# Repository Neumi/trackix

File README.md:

# trackix bike tracker
trackix is an Arduino based LORAWAN / GPS tracker that fits into the rear light of a bicycle and pushes location data to The Things Network. This data can be fetched using the TTN API. 

Facts:
- Arduino based (Atmega 368 @ 8Mhz)
- super low power in standby
- GPS for localization
- RFM95 / SIM800l for communication
- 3.3v logic voltage
- 3.7v buffer battery
- charging from 6V bike dynamo
- embedded into rear light

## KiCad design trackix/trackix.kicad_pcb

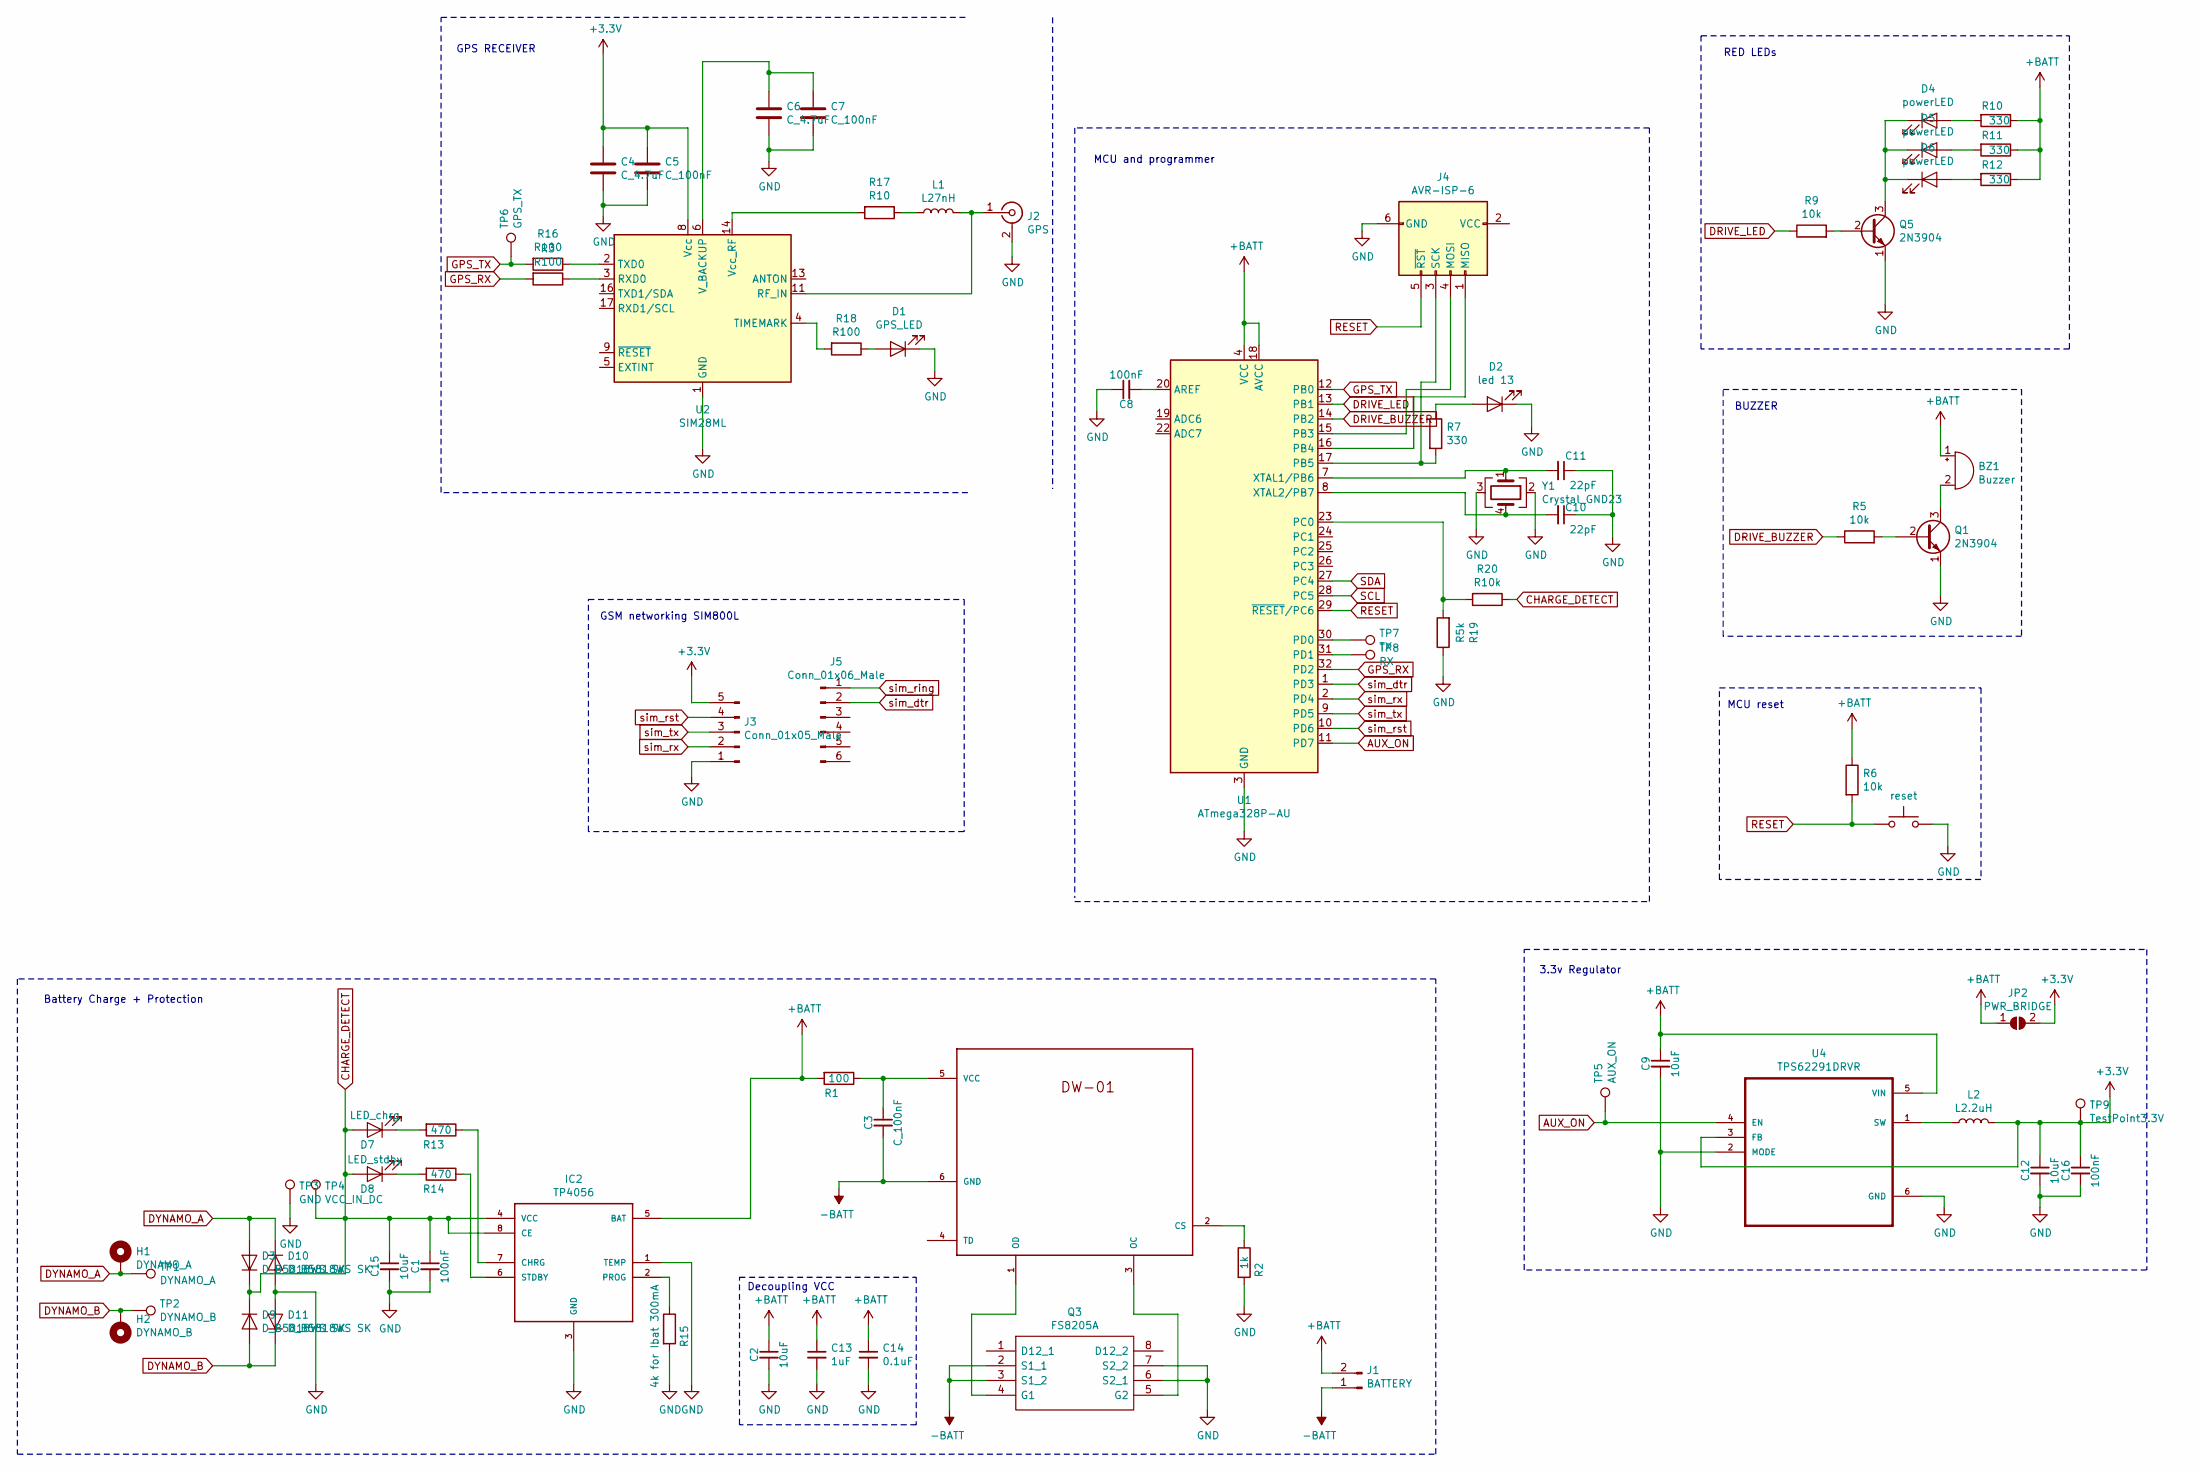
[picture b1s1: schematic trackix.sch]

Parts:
BZ1: Buzzer; Buzzer_Murata_PKMCS0909E4000-R1
C1, C8, C16: 100nF; C_0805
C2, C9, C12, C15: 10uF; C_1206
C3, C5, C7: C_100nF; C_0805
C4, C6: C_4.7uF; C_1206
C10, C11: 22pF; C_0805
C13: 1uF; C_1206
C14: 0.1uF; C_0805
D1: GPS_LED; LED_0805
D2: led 13; LED_0805
D3, D9, D10, D11: D_B5818WS SK; D_SOD-323
D4, D5: powerLED; LED_D5.0mm_Horizontal_O1.27mm_Z3.0mm
D6: powerLED; LED_D5.0mm
D7: LED_chrg; LED_0805
D8: LED_stdby; LED_0805
H1: DYNAMO_A; MountingHole_2.2mm_M2_ISO14580_Pad
H2: DYNAMO_B; MountingHole_2.2mm_M2_ISO14580_Pad
IC2: TP4056; HTSOP-8-1EP_3.9x4.9mm_Pitch1.27mm_ThermalVias_LargeCopper
J1: BATTERY; Pin_Header_Straight_1x02_Pitch2.54mm
J2: GPS; Molex_Microcoaxial_RF
J3: Conn_01x05_Male; Pin_Header_Straight_1x05_Pitch2.54mm
J4: AVR-ISP-6; Socket_Strip_Straight_2x03_Pitch2.54mm_SMD
J5: Conn_01x06_Male; Pin_Header_Straight_1x06_Pitch2.54mm
JP2: PWR_BRIDGE; SolderJumper-2_P1.3mm_Open_RoundedPad1.0x1.5mm
L1: L27nH; L_0402
L2: L2.2uH; L_1210
Q1, Q5: 2N3904; SOT-23W_Handsoldering
Q3: FS8205A; TSSOP-8_4.4x3mm_Pitch0.65mm; Manufacturer_Part_Number FS8205A
R1: 100; R_0805
R2: 1k; R_0805
R3, R16, R18: R100; R_0805
R5, R6, R9: 10k; R_0805
R7, R10, R11, R12: 330; R_0805
R13, R14: 470; R_0805
R15: 4k for Ibat 300mA; R_0805
R17: R10; R_0805
R19: R5k; R_0805
R20: R10k; R_0805
TP1: DYNAMO_A; Test_Point_Pad_1.0x1.0mm
TP2: DYNAMO_B; Test_Point_Pad_1.0x1.0mm
TP3: GND; Test_Point_Pad_1.0x1.0mm
TP4: VCC_IN_DC; Test_Point_Pad_1.0x1.0mm
TP5: AUX_ON; Test_Point_Pad_1.0x1.0mm
TP6: GPS_TX; Test_Point_Pad_1.0x1.0mm
TP7: TX; Test_Point_Pad_1.0x1.0mm
TP8: RX; Test_Point_Pad_1.0x1.0mm
TP9: TestPoint3.3V; Test_Point_Pad_1.0x1.0mm
U1: ATmega328P-AU; TQFP-32_7x7mm_Pitch0.8mm
U2: SIM28ML; XCVR_SIM28ML
U3: DW-01; TSOT-23-6
U4: TPS62291DRVR; SON65P200X200X80-7N
Y1: Crystal_GND23; Crystal_SMD_3225-4pin_3.2x2.5mm_HandSoldering
reset1: reset; SW_SPST_B3U-1000P

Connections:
+3V3: C4.1, C5.1, C12.1, C16.1, J3.5, JP2.2 (B), L2.2, TP9.1, U2.8 (Vcc), U4.3 (FB)
+BATT: BZ1.1 (-), C2.1, C9.1, C13.1, C14.1, IC2.5 (BAT), J1.2, JP2.1 (A), R1.2, R6.1, R10.1, R11.1, R12.1, U1.4 (VCC), U1.6 (VCC), U1.18 (AVCC), U4.5 (VIN)
-BATT: C3.2, J1.1, Q3.2 (S1_1), Q3.3 (S1_2), U3.6 (GND)
AUX_ON: TP5.1, U1.11 (PD7), U4.4 (EN)
CHARGE_DETECT: C1.1, C15.1, D3.1 (K), D7.2 (A), D8.2 (A), D9.1 (K), IC2.4 (VCC), IC2.8 (CE), R20.1, TP4.1
DRIVE_BUZZER: R5.1, U1.14 (PB2)
DRIVE_LED: R9.1, U1.13 (PB1)
DYNAMO_A: D3.2 (A), D10.1 (K), H1.1, TP1.1
DYNAMO_B: D9.2 (A), D11.1 (K), H2.1, TP2.1
GND: C1.2, C2.2, C4.2, C5.2, C6.2, C7.2, C8.1, C9.2, C10.1, C11.1, C12.2, C13.2, C14.2, C15.2, C16.2, D1.1 (K), D2.1 (K), D10.2 (A), D11.2 (A), IC2.1 (TEMP), IC2.3 (GND), J2.2 (Ext), J3.1, J4.6 (GND), Q1.1 (E), Q3.6 (S2_1), Q3.7 (S2_2), Q5.1 (E), R2.2, R15.2, R19.1, TP3.1, U1.3 (GND), U1.5 (GND), U1.21 (GND), U2.1 (GND), U2.10 (GND), U2.12 (GND), U4.2 (MODE), U4.6 (GND), Y1.2, Y1.3, reset1.2
GPS_RX: R3.2, U1.32 (PD2)
GPS_TX: R16.2, TP6.1, U1.12 (PB0)
unnamed 12: C11.2, U1.7 (XTAL1/PB6), Y1.1; also elsewhere on the board
unnamed 13: C10.2, U1.8 (XTAL2/PB7), Y1.4; also elsewhere on the board
unnamed: BZ1.2 (+), Q1.3 (C)
unnamed: C3.1, R1.1, U3.5 (VCC)
unnamed: C6.1, C7.1, U2.6 (V_BACKUP)
unnamed: C8.2, U1.20 (AREF)
unnamed: D1.2 (A), R18.1
unnamed: D2.2 (A), R7.1
unnamed: D4.1 (K), D5.1 (K), D6.1 (K), Q5.3 (C)
unnamed: D4.2 (A), R10.2
unnamed: D5.2 (A), R11.2
unnamed: D6.2 (A), R12.2
unnamed: D7.1 (K), R13.2
unnamed: D8.1 (K), R14.2
unnamed: IC2.2 (PROG), R15.1
unnamed: IC2.6 (STDBY), R14.1
unnamed: IC2.7 (CHRG), R13.1
unnamed: J2.1 (In), L1.2, U2.11 (RF_IN)
unnamed: J4.1 (MISO), U1.16 (PB4)
unnamed: J4.3 (SCK), R7.2, U1.17 (PB5)
unnamed: J4.4 (MOSI), U1.15 (PB3)
unnamed: L1.1, R17.1
unnamed: L2.1, U4.1 (SW)
unnamed: Q1.2 (B), R5.2
unnamed: Q3.4 (G1), U3.1 (OD)
unnamed: Q3.5 (G2), U3.3 (OC)
unnamed: Q5.2 (B), R9.2
unnamed: R2.1, U3.2 (CS)
unnamed: R3.1, U2.3 (RXD0)
unnamed: R16.1, U2.2 (TXD0)
unnamed: R17.2, U2.14 (Vcc_RF)
unnamed: R18.2, U2.4 (TIMEMARK)
unnamed: R19.2, R20.2, U1.23 (PC0)
unnamed: TP7.1, U1.30 (PD0)
unnamed: TP8.1, U1.31 (PD1)
RESET: J4.5 (~RST), R6.2, U1.29 (~RESET~/PC6), reset1.1
SCL: U1.28 (PC5)
SDA: U1.27 (PC4)
sim_dtr: J5.2, U1.1 (PD3)
sim_ring: J5.1
sim_rst: J3.4, U1.10 (PD6)
sim_rx: J3.2, U1.2 (PD4)
sim_tx: J3.3, U1.9 (PD5)

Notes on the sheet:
3.3v Regulator
Battery Charge + Protection
RED LEDs
BUZZER
Decoupling VCC
MCU reset
MCU and programmer
GSM networking SIM800L
GPS RECEIVER

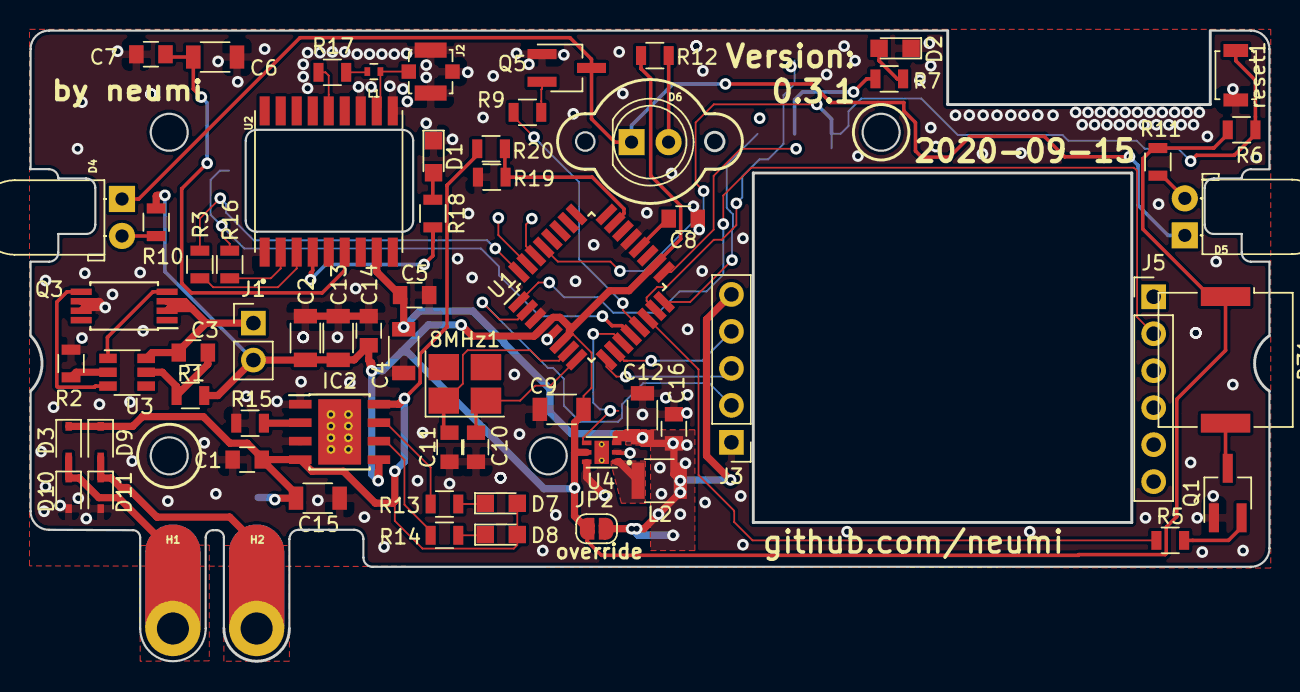
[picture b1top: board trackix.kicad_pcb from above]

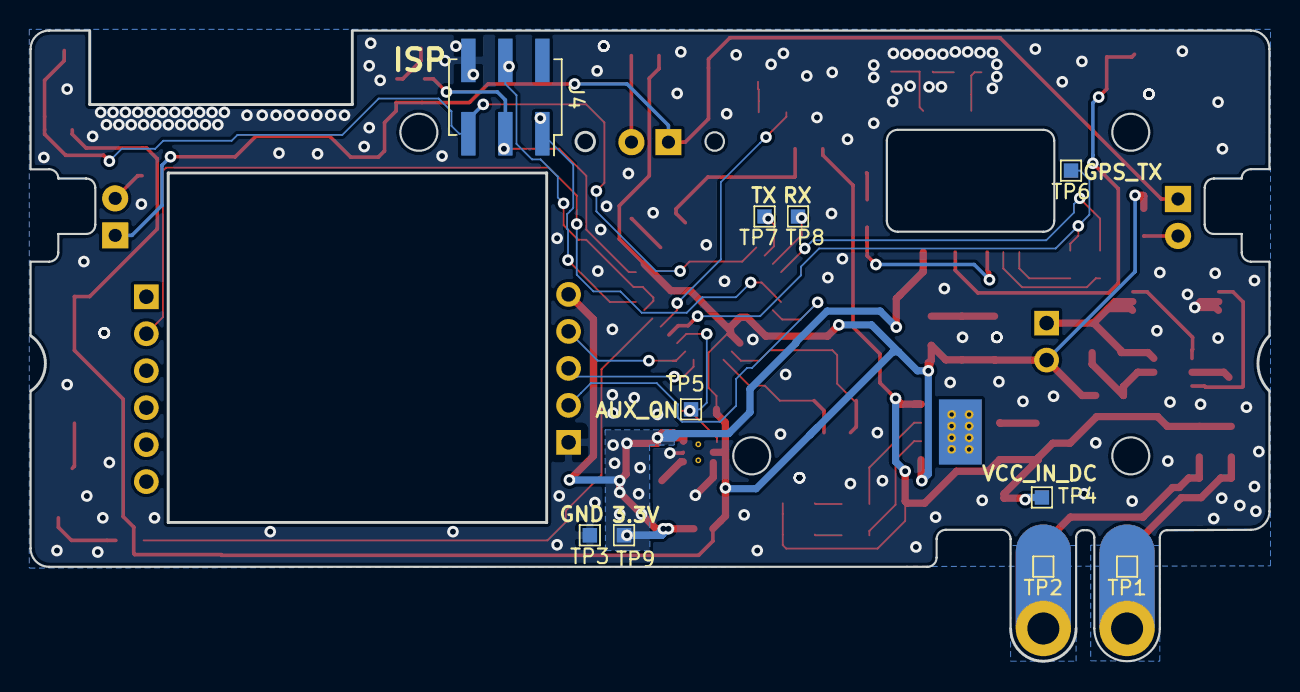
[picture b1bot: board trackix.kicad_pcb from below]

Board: 2 copper layers, 85.1 x 43.3 mm, 75 parts (10 on the bottom side), 52 nets.

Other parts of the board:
8MHz1: Crystal; Crystal_SMD_3225-4pin_3.2x2.5mm_HandSoldering

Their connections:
unnamed 12: 8MHz1.1; also elsewhere on the board
unnamed 13: 8MHz1.2; also elsewhere on the board

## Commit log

2019-02-17 Add files via upload
    initial commit kicad files
2019-02-18 layout changes 1
2019-02-18 layout changes 2
2019-03-11 prototype 0.1 state
2020-08-18 all things so far
2020-08-18 added firmware for ttn test
2020-09-15 schematic ready for sim800L
2020-10-01 added gsm version
